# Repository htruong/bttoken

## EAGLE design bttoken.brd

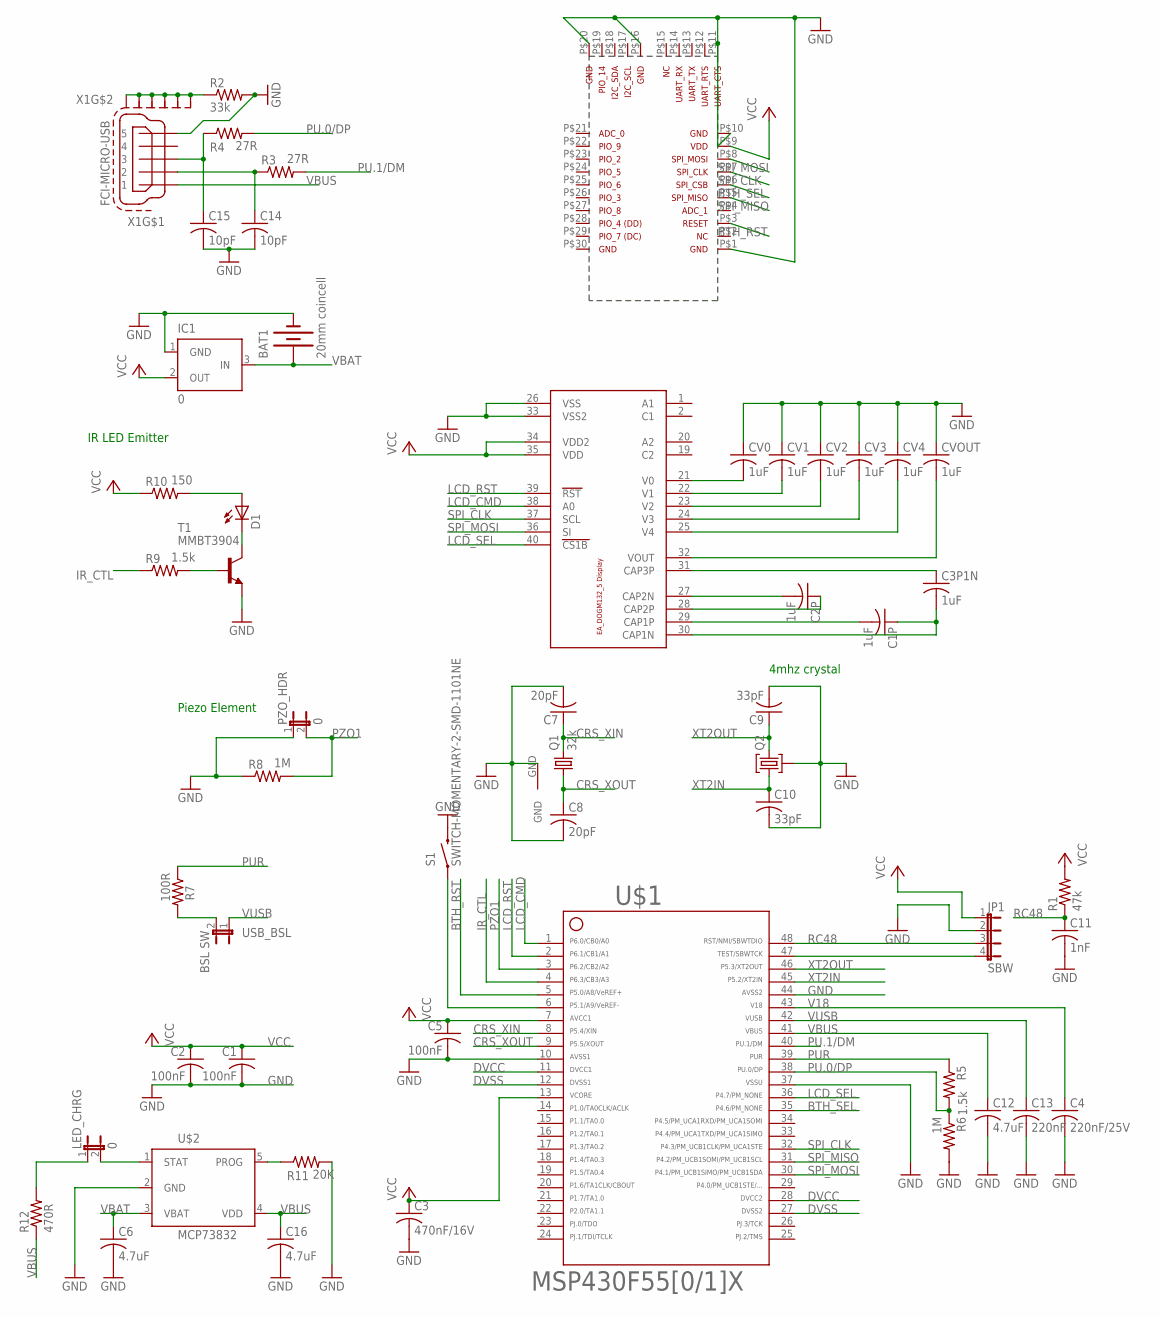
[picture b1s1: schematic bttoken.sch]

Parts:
BAT1: 20mm coincell; BAT-HLD-001
C1, C2, C5: 100nF; C0805
C1P, C2P, C3P1N: 1uF; C0805
C3: 470nF/16V; C0805
C4: 220nF/25V; C0805
C6, C12, C16: 4.7uF; C0805
C7, C8: 20pF; C0805
C9, C10: 33pF; C0805
C11: 1nF; C0805
C13: 220nF; C0805
C14, C15: 10pF; C0805
CV0, CV1, CV2, CV3, CV4: 1uF; C0805
CVOUT: 1uF; C0805
D1: SFH482
IC1: 0; SOT23
JP1: SBW; JP4
LED_CHRG: 0; JP1
PZO_HDR: 0; JP1
Q1: 32k; TC26H-SMT
Q2: 10G7A-12.5KHZ; HC49U
R1: 47k; R0805
R2: 33k; R0805
R3, R4: 27R; R0805
R5, R9: 1.5k; R0805
R6, R8: 1M; R0805
R7: 100R; R0805
R10: 150; R0805
R11: 20K; R0805
R12: 470R; R0805
S1: SWITCH-MOMENTARY-2-SMD-1101NE; TACTILE-SWITCH-1101NE
T1: MMBT3904; SOT23-BEC
U$1: F55[0/1]X---PT48; PT48
U$2: MCP73832; SOT23-5
U$11: DISPLAY_EA_DOGM132_EA_DOG-M_DISPLAY; DISPLAY_EA_DOGM132_E_DOG-M_DISPLAY
U$13: BR-LE4.0-S3-NC; BR-LE4.0-X2A-NC
USB_BSL: BSL SW; JP1
X1: FCI-MICRO-USB; FCI-MICRO-USB5

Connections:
BTH_RST: U$1.5, U$13.P$3
BTH_SEL: U$1.35, U$13.P$6
CRS_XIN: C7.1, Q1.2, U$1.8
CRS_XOUT: C8.1, Q1.1, U$1.9
DVCC: U$1.11, U$1.28
DVSS: U$1.12, U$1.27
GND: BAT1.P$1- (-), C1.2, C2.2, C3.2, C4.2, C5.2, C6.2, C7.2, C8.2, C9.2, C10.2, C11.2, C12.2, C13.2, C14.2, C15.2, C16.2, CV0.1, CV1.1, CV2.1, CV3.1, CV4.1, CVOUT.1, IC1.1 (GND), JP1.2, PZO_HDR.1, Q1.GND, Q2.2, R2.2, R6.2, R8.1, R11.2, S1.P$2 (2), T1.E, U$1.10, U$1.37, U$1.44, U$2.2 (GND), U$11.26 (VSS), U$11.33 (VSS2), U$13.P$1, U$13.P$10, U$13.P$11, U$13.P$16, U$13.P$20, X1.5
IR_CTL: R9.1, U$1.4
LCD_CMD: U$1.1, U$11.38 (A0)
LCD_RST: U$1.2, U$11.39 (RST)
LCD_SEL: U$1.36, U$11.40 (CS1B)
unnamed: R2.1, X1.M1 (S1), X1.M2 (S2), X1.M3 (S3), X1.M4 (S4), X1.M5 (S5), X1.M6 (S6)
unnamed: R11.1, U$2.5 (PROG)
unnamed: LED_CHRG.2, U$2.1 (STAT)
unnamed: LED_CHRG.1, R12.2
unnamed: D1.A, R10.2
unnamed: JP1.4, U$1.47
unnamed: C14.1, R3.1, X1.2
unnamed: R7.2, USB_BSL.2
unnamed: CV1.2, U$11.22 (V1)
unnamed: R9.2, T1.B
unnamed: C15.1, R4.1, X1.3
unnamed: S1.P$1 (1), U$1.6
unnamed: D1.K (C), T1.C
unnamed: CV2.2, U$11.23 (V2)
unnamed: CV3.2, U$11.24 (V3)
unnamed: CV4.2, U$11.25 (V4)
unnamed: CVOUT.2, U$11.32 (VOUT)
unnamed: C3P1N.1, U$11.31 (CAP3P)
unnamed: CV0.2, U$11.21 (V0)
unnamed: C2P.2, U$11.27 (CAP2N)
unnamed: C2P.1, U$11.28 (CAP2P)
unnamed: C1P.2, U$11.29 (CAP1P)
unnamed: C1P.1, C3P1N.2, U$11.30 (CAP1N)
PU.0/DP: R4.2, R5.2, R6.1, U$1.38
PU.1/DM: R3.2, U$1.40
PUR: R5.1, R7.1, U$1.39
PZO1: PZO_HDR.2, R8.2, U$1.3
RC48: C11.1, JP1.3, R1.1, U$1.48
SPI_CLK: U$1.32, U$11.37 (SCL), U$13.P$7
SPI_MISO: U$1.31, U$13.P$5
SPI_MOSI: U$1.30, U$11.36 (SI), U$13.P$8
V18: C4.1, U$1.43
VBAT: BAT1.P$2+ (+), BAT1.P$3+ (+), C6.1, IC1.3 (IN), U$2.3 (VBAT)
VBUS: C12.1, C16.1, R12.1, U$1.41, U$2.4 (VDD), X1.1
VCC: C1.1, C2.1, C3.1, C5.1, IC1.2 (OUT), JP1.1, R1.2, R10.1, U$1.7, U$1.13, U$11.34 (VDD2), U$11.35 (VDD), U$13.P$9
VUSB: C13.1, U$1.42, USB_BSL.1
XT2IN: C10.1, Q2.1, U$1.45
XT2OUT: C9.1, Q2.3, U$1.46

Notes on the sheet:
4mhz crystal
Piezo Element
IR LED Emitter

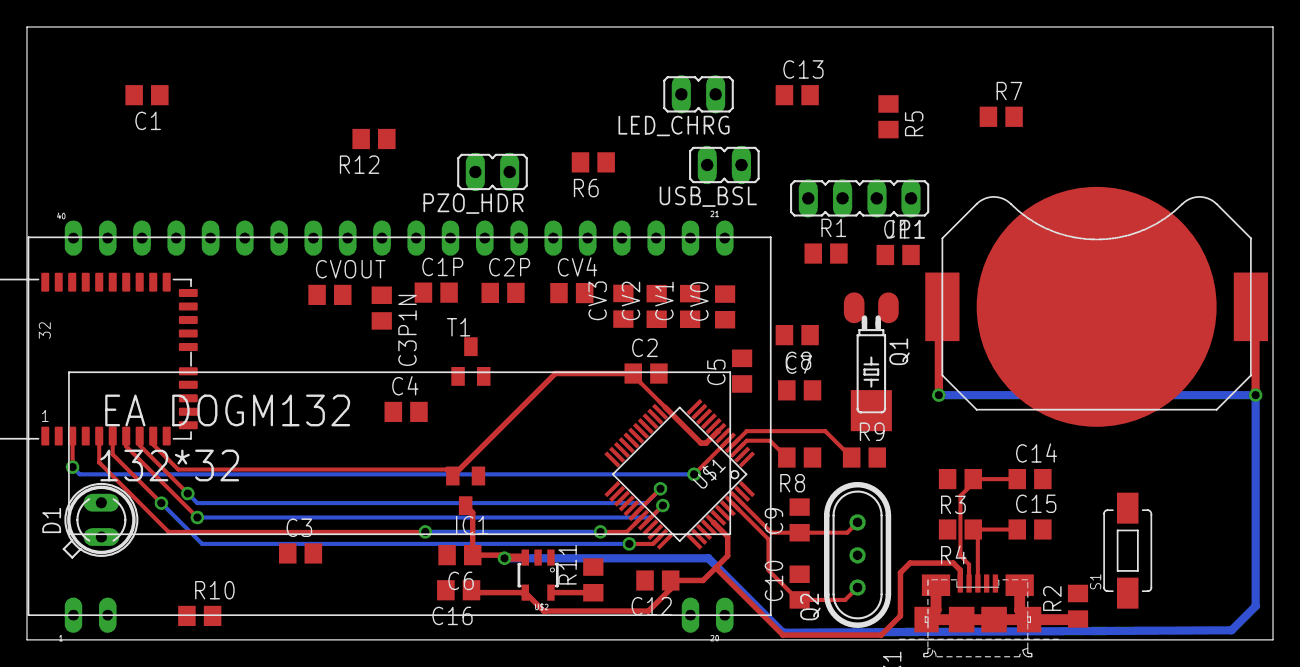
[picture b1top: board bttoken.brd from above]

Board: 2 copper layers, 92.3 x 45.4 mm, 53 parts (0 on the bottom side), 49 nets.

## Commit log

2013-03-09 Added updated library file.
2013-03-09 Added an image of the original breakout board.
2013-03-09 Cleaned up stuff
2013-03-09 Cleaned up stuff part 2 - removed headers
2013-03-09 Added wires to the bluetooth module
2013-03-09 Connected all wires together
2013-03-09 Added the piezo element, migrated to eagle 6, added Sparkfun eagle lib
2013-03-09 Fixed errors warnings and stuff
2013-03-10 Added local component library.
2013-03-10 New board - Regulator, fix so that eagle doesn't complain etc
2013-03-10 Added new charger circuit
2013-03-10 Temp CR2032 batt holder until we have a better one
2013-03-10 Added Linx CR2025/CR2032 battery holder.
2013-03-10 Checkpoint
2013-03-10 Auto routing works
2013-03-10 A little optimization
2013-03-10 Updated the Bluetooth module to remove pads that aren't connected.
    Added tRestrict and bRestrict areas too.
2013-03-10 Added support files for OSHPark processing.
2013-03-11 New revision with moved quartz, changed filter, etc. Broke autorouting

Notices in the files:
parts and their libraries:
SparkFun-Electromechanical: Licensing: CC v3.0 Share-Alike You are welcome to use this library for commercial purposes.
